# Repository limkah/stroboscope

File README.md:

# Stroboscope
Basic stroboscope implementation for measuring shaft/pulley RPM.

Prototype implementation is with P-channel power MOSFET driving a 12V high power LED as a high-side switch. Switching is done with a smaller N-channel MOSFET from the logic pin of a microcontroller (in this case an Arduino for the initial setup and testing). Display is going to be a 2x16 character display, since that's what I have in the parts bin, may switch to a 7 segment if I have to order parts.

Status:

- Basic board layout added for planning purposes.
- Added Rev 0 of firmware (functioning prototype).

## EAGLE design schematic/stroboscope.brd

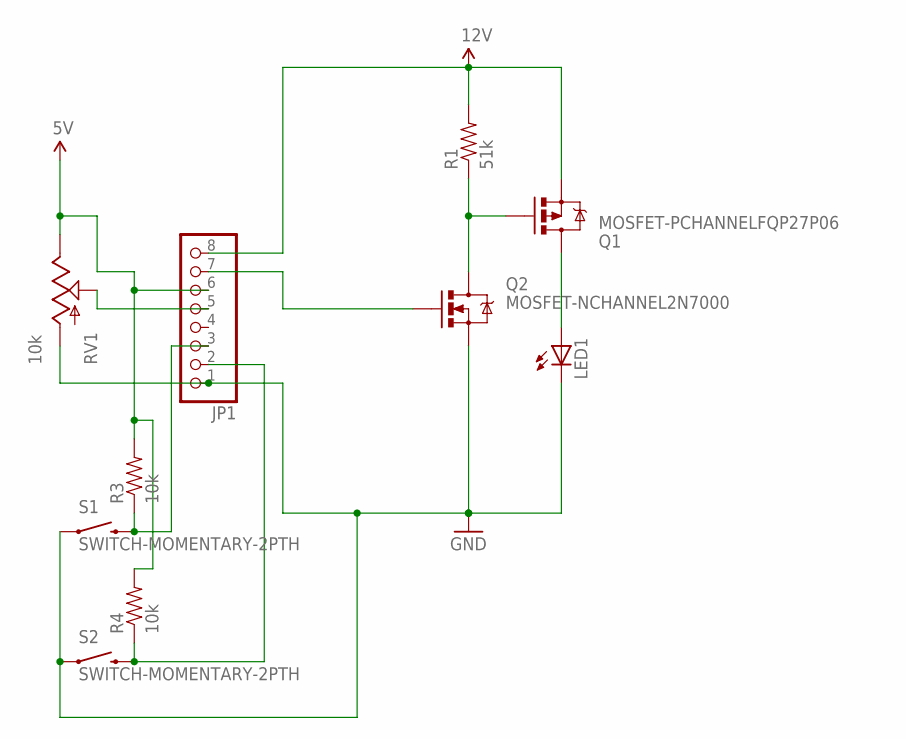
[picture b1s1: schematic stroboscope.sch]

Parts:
JP1: PINHD-1X8BIG; 1X08-BIG
LED1: LEDSQR2X5; LED2X5
Q1: MOSFET-PCHANNELFQP27P06; TO220V
Q2: MOSFET-NCHANNEL2N7000; TO-92
R1: 51k; AXIAL-0.4
R3, R4: 10k; AXIAL-0.4
RV1: 10k; ALPS_POT
S1, S2: SWITCH-MOMENTARY-2PTH; TACTILE-PTH

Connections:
5V: JP1.6, R3.P$2 (2), R4.P$2 (2), RV1.P$1 (E)
12V: JP1.8, Q1.3 (S), R1.P$2 (2)
GND: JP1.1, LED1.K (C), Q2.1 (S), RV1.P$3 (A), S1.1, S2.1
OUT: LED1.A, Q1.2 (D)
POT_SIG: JP1.5, RV1.P$2 (S)
PWR_GATE: Q1.1 (G), Q2.3 (D), R1.P$1 (1)
SIG: JP1.7, Q2.2 (G)
SW1_SIG: JP1.3, R3.P$1 (1), S1.3 (2)
SW2_SIG: JP1.2, R4.P$1 (1), S2.3 (2)

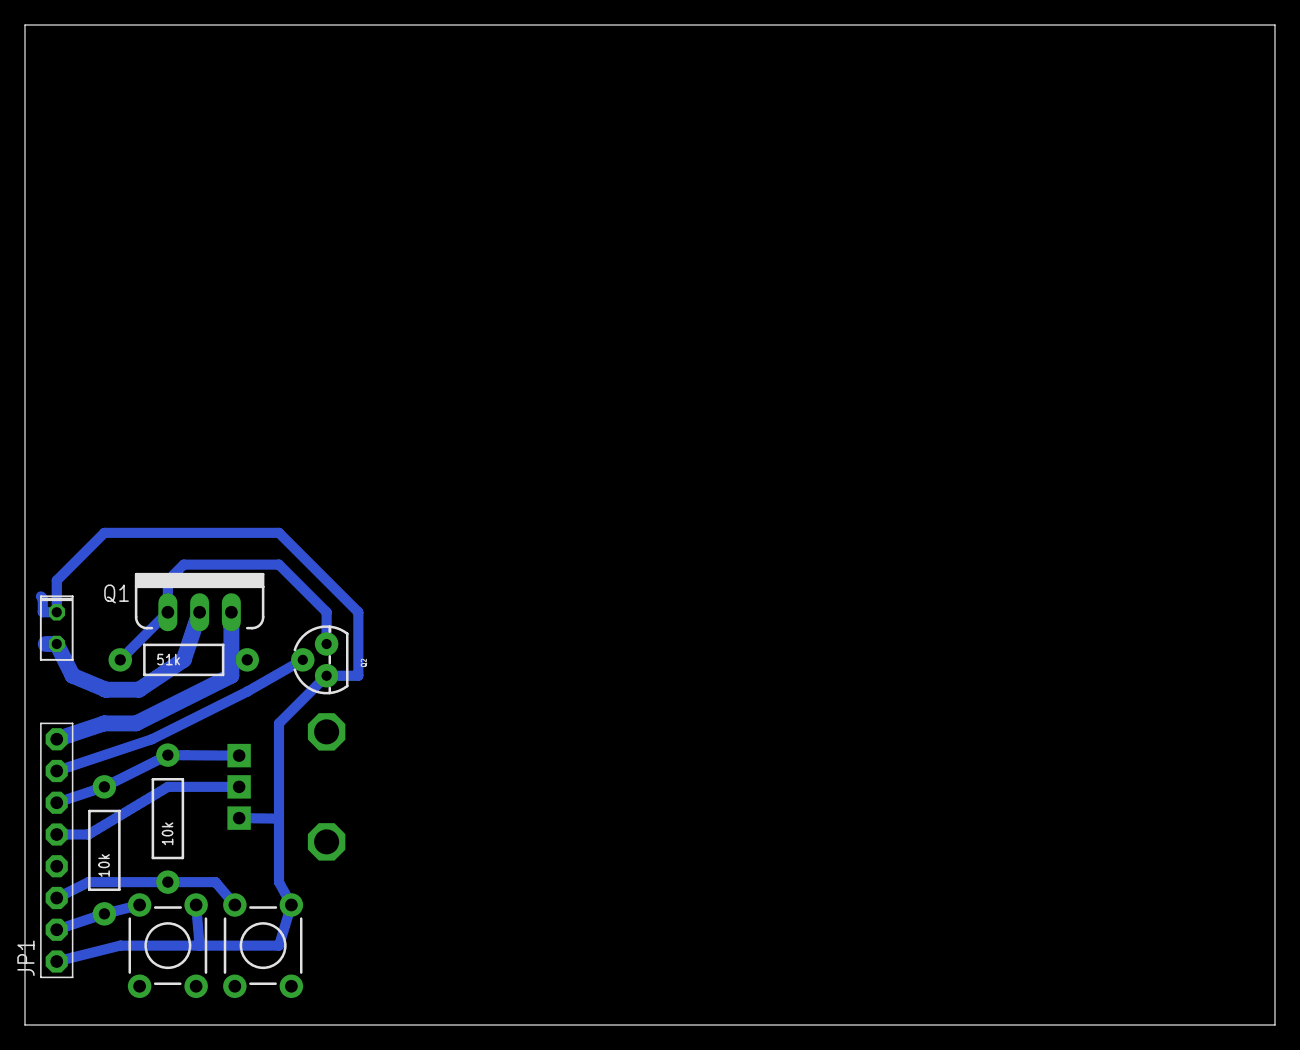
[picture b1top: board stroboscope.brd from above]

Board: 2 copper layers, 100.0 x 80.0 mm, 10 parts (0 on the bottom side), 9 nets.

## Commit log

2018-02-27 Update of readme to include meaningful information
2018-03-07 Added initial version of schematic/board files
    Temporary layout for parts as an "extension" board for connection to an
    arduino or other dev kit. Does not represent a full, functional device,
    but just as a planning exercise. Will likely have the final circuit on
    perfboard with a bunch of auxilaries connected, since this will likely
    only be used a few times and doesn't need to be a polished device.
2018-03-07 Minor update to status in readme.
2018-03-19 Added Rev 0 of Arduino firmware.
    Functioning initial implementation of the Arduino firmware (used on
    Arduino Uno), may update and clean up a few things, but it's mostly in
    its final form. Will likely be using a Teensy LC or smaller Arduino
    board, so may need to update some of the pin numbering. Corresponding
    update to schematic will be made when final board is decided on.
2018-03-19 Updated readme to include firmware R0

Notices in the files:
parts and their libraries:
SparkFun-DiscreteSemi: Licensing: Creative Commons ShareAlike 4.0 International - https://creativecommons.org/licenses/by-sa/4.0
